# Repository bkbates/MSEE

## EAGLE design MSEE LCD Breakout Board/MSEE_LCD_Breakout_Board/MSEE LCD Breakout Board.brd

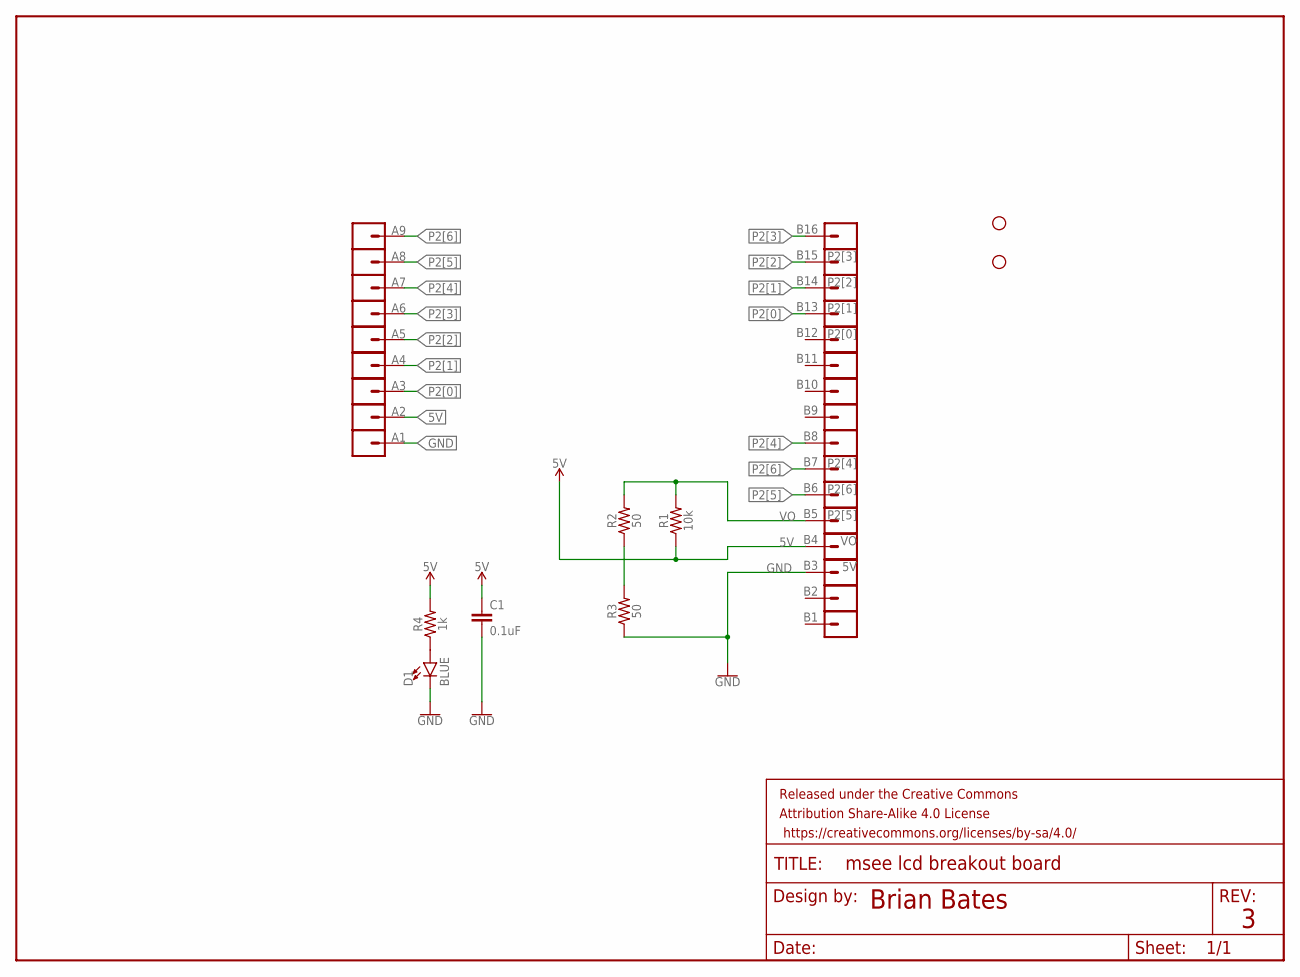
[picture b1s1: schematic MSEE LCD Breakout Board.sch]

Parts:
5V: A2; 1X01_LONGPAD
B1, B2, B9, B10, B11, B12: CONN_01PTH_LONGPAD; 1X01_LONGPAD
B3: GND; 1X01_LONGPAD
B4: 5V; 1X01_LONGPAD
B5: VO; 1X01_LONGPAD
B6: P2[5]; 1X01_LONGPAD
B7: P2[6]; 1X01_LONGPAD
B8: P2[4]; 1X01_LONGPAD
B13: P2[0]; 1X01_LONGPAD
B14: P2[1]; 1X01_LONGPAD
B15: P2[2]; 1X01_LONGPAD
B16: P2[3]; 1X01_LONGPAD
C1: 0.1uF; 0603
D1: BLUE; LED-0603
FRAME1: FRAME-LETTERNO_PACKAGE; DUMMY
GND: A1; 1X01_LONGPAD
H2, H4: STAND-OFF
P2[0]: A3; 1X01_LONGPAD
P2[1]: A4; 1X01_LONGPAD
P2[2]: A5; 1X01_LONGPAD
P2[3]: A6; 1X01_LONGPAD
P2[4]: A7; 1X01_LONGPAD
P2[5]: A8; 1X01_LONGPAD
P2[6]: A9; 1X01_LONGPAD
R1: 10k; 0603
R2, R3: 50; 0603
R4: 1k; 0603

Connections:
5V: 5V.1, B4.1, C1.1, R1.1, R4.2
'': C1.2
GND: B3.1, D1.C, GND.1, R3.1
unnamed: D1.A, R4.1
unnamed: R2.1, R3.2
P2[0]: B13.1, P2[0].1
P2[1]: B14.1, P2[1].1
P2[2]: B15.1, P2[2].1
P2[3]: B16.1, P2[3].1
P2[4]: B8.1, P2[4].1
P2[5]: B6.1, P2[5].1
P2[6]: B7.1, P2[6].1
VO: B5.1, R1.2, R2.2

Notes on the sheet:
Brian Bates

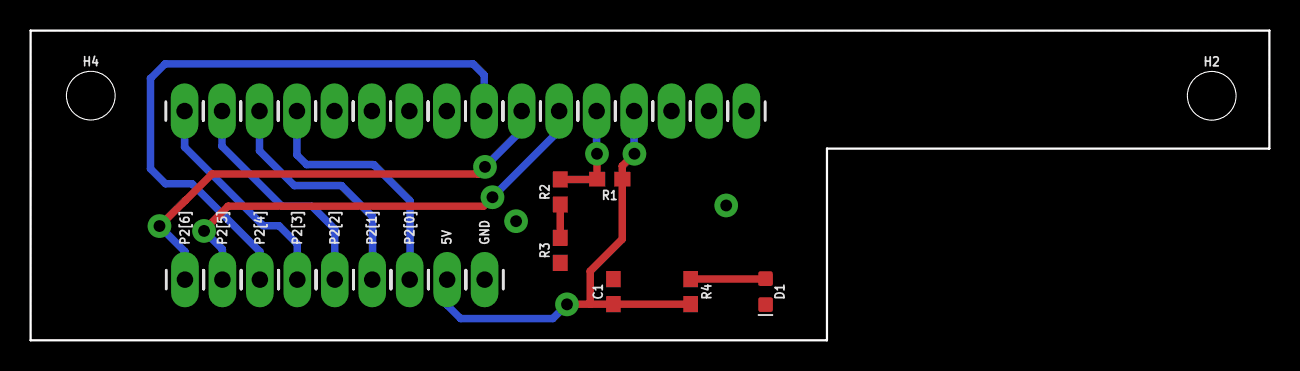
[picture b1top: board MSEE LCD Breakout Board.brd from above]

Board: 2 copper layers, 84.0 x 21.0 mm, 34 parts (0 on the bottom side), 12 nets.

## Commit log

2020-01-27 LCD Breakout Board v1
2020-01-30 MSEE LCD Breakout Board v3
2020-01-30 Cleanup

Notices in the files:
parts and their libraries:
SparkFun-Capacitors: Licensing: Creative Commons ShareAlike 4.0 International - https://creativecommons.org/licenses/by-sa/4.0
SparkFun-Aesthetics: Released under the Creative Commons Attribution Share-Alike 4.0 License
SparkFun-Aesthetics: https://creativecommons.org/licenses/by-sa/4.0
